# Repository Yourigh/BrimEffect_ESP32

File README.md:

# BrimEffect_ESP32
 ESP32 board with interface for WS2812 LED strip, connected MIC and IR remote receiver, including FW and 3D prited box
 
# 3D prited box

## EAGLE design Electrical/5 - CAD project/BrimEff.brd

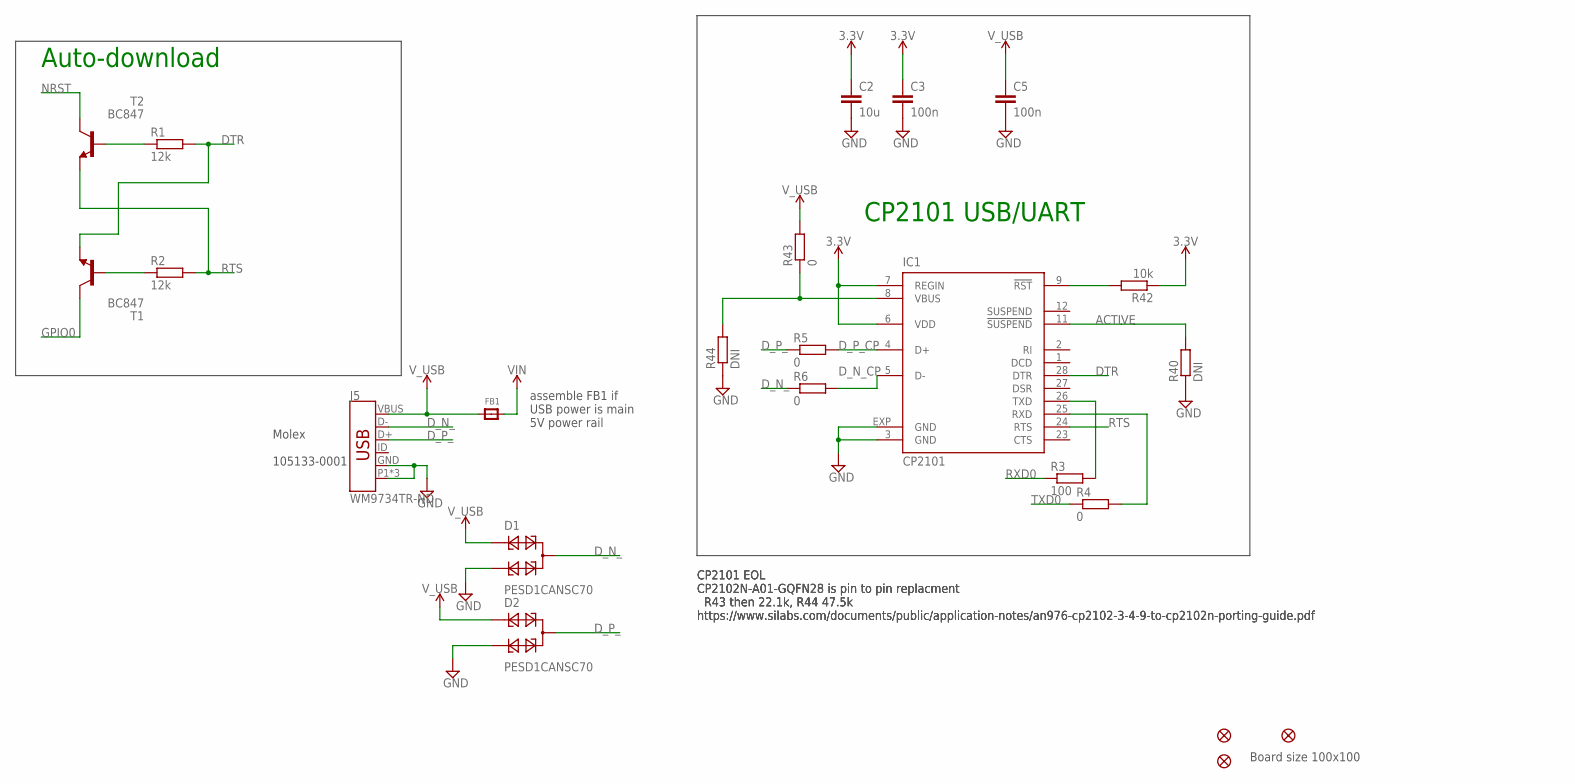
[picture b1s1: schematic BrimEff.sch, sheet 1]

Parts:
C2: 10u; C0603K; PARTNO GRM188R61A106KE69J
C3, C5: 100n; C0603K; PARTNO CC0603KRX7R8BB104
D1, D2: PESD1CANSC70; SOT323-R; PARTNO PESD1CAN-UX
FB1: FERRITE; 0603; PARTNO BLM18PG121SN1D
FID1, FID2, FID4: FIDUCIAL""; FIDUCIAL_1MM
IC1: CP2101; MLP28; PARTNO CP2101-GM
J5: WM9734TR-ND; USB-B-MICRO-SMD_VERT; PARTNO 105133-0001
R1, R2: 12k; R0603; PARTNO RC0603FR-0712KL
R3: 100; R0603; PARTNO CRCW0603100RFKEAC
R4, R5, R6, R43: 0; R0603; PARTNO CRCW06030000Z0EAC
R40, R44: DNI; R0603; PARTNO CRCW06030000Z0EAC
R42: 10k; R0603; PARTNO CRCW060310K0JNEAC
T1, T2: BC847; SOT23; PARTNO BC847A-TP

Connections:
3.3V: C2.1, C3.1, IC1.6 (VDD), IC1.7 (REGIN), R42.1; also elsewhere on the board
ACTIVE: IC1.11 (!SUSPEND), R40.2
DTR: IC1.28 (DTR), R1.2, T1.2 (E)
D_N_: D1.3, J5.D-, R6.1
D_N_CP: IC1.5 (D-), R6.2
D_P_: D2.3, J5.D+, R5.1
D_P_CP: IC1.4 (D+), R5.2
GND: C2.2, C3.2, C5.2, D1.2, D2.2, IC1.3 (GND), IC1.EXP (GND), J5.GND, J5.P1 (SHIELD), J5.P2 (SHIELD), J5.P3 (SHIELD), R40.1, R44.1; also elsewhere on the board
GPIO0: T1.3 (C); also elsewhere on the board
unnamed: R1.1, T2.1 (B)
unnamed: R2.1, T1.1 (B)
unnamed: IC1.9 (!RST), R42.2
unnamed: IC1.8 (VBUS), R43.1, R44.2
NRST: T2.3 (C); also elsewhere on the board
RTS: IC1.24 (RTS), R2.2, T2.2 (E)
RXD0: R3.1; also elsewhere on the board
RXD0_CP2101IN: IC1.26 (TXD), R3.2
TXD0: R4.1; also elsewhere on the board
TXD0_CP2101: IC1.25 (RXD), R4.2
VIN: FB1.2; also elsewhere on the board
V_USB: C5.1, D1.1, D2.1, FB1.1, J5.VBUS, R43.2

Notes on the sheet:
CP2101 USB/UART
Auto-download
Board size 100x100
Molex 105133-0001
CP2101 EOL CP2102N-A01-GQFN28 is pin to pin replacment R43 then 22.1k, R44 47.5k https://www.silabs.com/documents/public/application-notes/an976-cp2102-3-4-9-to-cp2102n-porting-guide.pdf
assemble FB1 if USB power is main 5V power rail

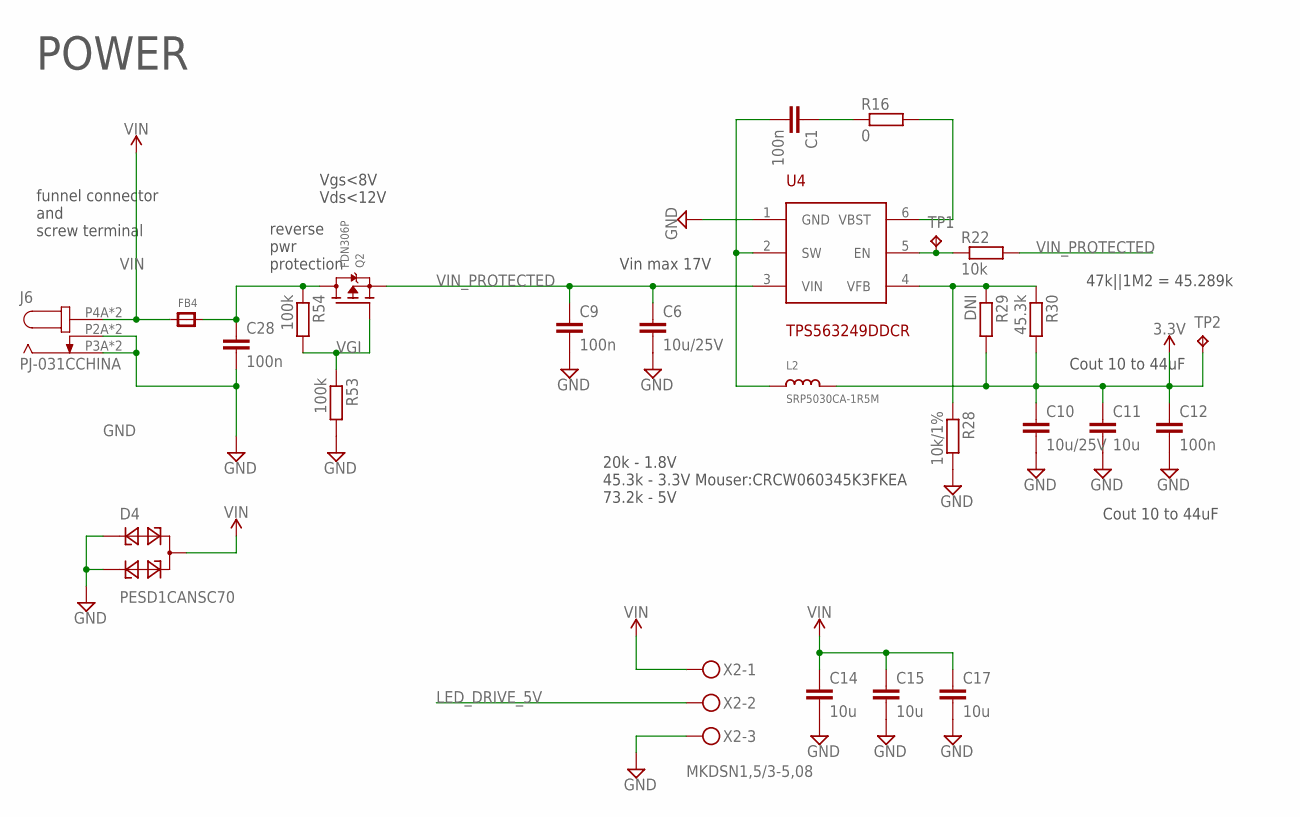
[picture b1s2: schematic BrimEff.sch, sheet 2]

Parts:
C1, C9, C12, C28: 100n; C0603K; PARTNO CC0603KRX7R8BB104
C6, C10: 10u/25V; C0603K; PARTNO GRM188R61E106KA73J
C11, C14, C15, C17: 10u; C0603K; PARTNO GRM188R61A106KE69J
D4: PESD1CANSC70; SOT323-R; PARTNO PESD1CAN-UX
FB4: FERRITE; 0603; PARTNO BLM18PG121SN1D
J6: PJ-031CCHINA; DC-005_5.5X2.1MM_JACK
L2: SRP5030CA-1R5M; SRP5030CA; PARTNO SRP5030CA-1R5M
Q2: FDN306P; SOT23-WIDE; PARTNO FDN306P
R16: 0; R0603; PARTNO CRCW06030000Z0EAC
R22: 10k; R0603; PARTNO CRCW060310K0JNEAC
R28: 10k/1%; R0603; PARTNO RN73R1JTTD1002D25
R29: DNI; R0603
R30: 45.3k; R0603; PARTNO ERJ-PB3D4532V
R53, R54: 100k; R0603; PARTNO CRCW0603100KFKEAC
TP1, TP2: TPTP10R; TP10R
U4: TPS563249DDCR; SOT23-6; PARTNO TPS563249DDCR
X2: MKDSN1,5/3-5,08

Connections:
3.3V: C10.1, C11.1, C12.1, L2.P$2 (2), R29.2, R30.2, TP2.TP; also elsewhere on the board
GND: C6.2, C9.2, C10.2, C11.2, C12.2, C14.2, C15.2, C17.2, C28.2, D4.1, D4.2, J6.P2A (3), J6.P2B (3), J6.P3A (2), J6.P3B (2), R28.2, R53.2, U4.1 (GND), X2.3; also elsewhere on the board
LED_DRIVE_5V: X2.2; also elsewhere on the board
unnamed: C1.1, R16.1
unnamed: C28.1, FB4.2, Q2.3 (D), R54.1
unnamed: R16.2, U4.6 (VBST)
unnamed: C1.2, L2.P$1 (1), U4.2 (SW)
unnamed: R22.1, TP1.TP, U4.5 (EN)
unnamed: R28.1, R29.1, R30.1, U4.4 (VFB)
VGI: Q2.1 (G), R53.1, R54.2
VIN: C14.1, C15.1, C17.1, D4.3, FB4.1, J6.P4A (1), J6.P4B (1), X2.1; also elsewhere on the board
VIN_PROTECTED: C6.1, C9.1, Q2.2 (S), R22.2, U4.3 (VIN); also elsewhere on the board

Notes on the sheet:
POWER
20k - 1.8V 45.3k - 3.3V Mouser:CRCW060345K3FKEA 73.2k - 5V
Cout 10 to 44uF
reverse pwr protection
Vgs<8V Vds<12V
Vin max 17V
funnel connector and screw terminal
47k||1M2 = 45.289k

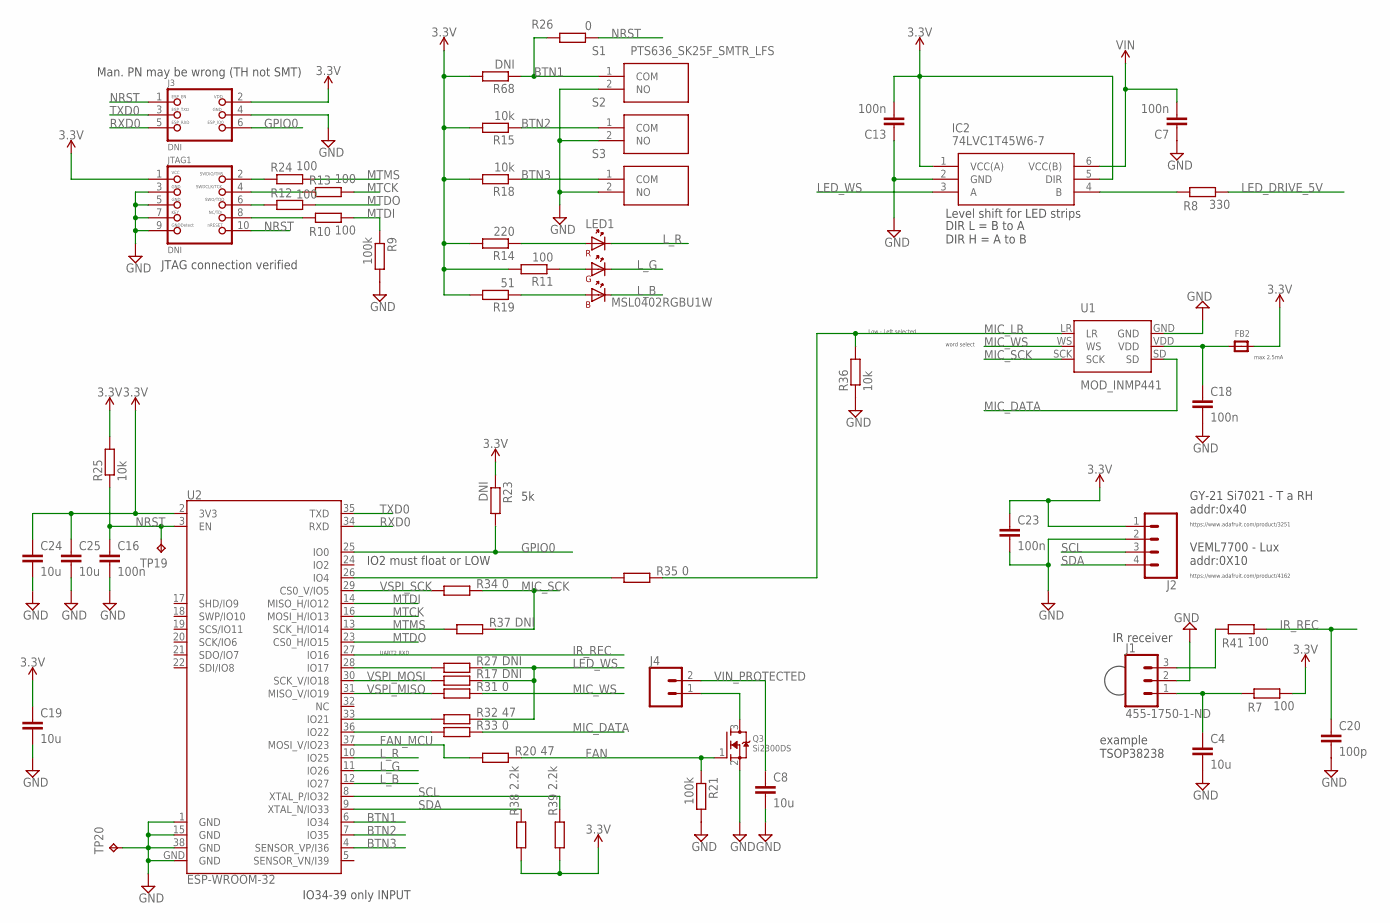
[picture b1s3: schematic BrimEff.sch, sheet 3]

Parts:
C4, C8, C19, C24, C25: 10u; C0603K; PARTNO GRM188R61A106KE69J
C7, C13, C16, C18, C23: 100n; C0603K; PARTNO CC0603KRX7R8BB104
C20: 100p; C0603K; PARTNO GRM188R61A106KE69J
FB2: FERRITE; 0603; PARTNO BLM18PG121SN1D
IC2: 74LVC1T45W6-7; SOT95P285X140-6N
J1: 455-1750-1-ND; 1X03
J2: CONN_04PTH; 1X04
J3: DNI; 2X03_1.27MM_SMT; PARTNO HTMS-103-03-T-D-SM
J4: CONN_02; 1X02
JTAG1: DNI; 2X05_1.27MM_SMT; PARTNO M50-3600542R
LED1: MSL0402RGBU1W; MSL0402RGBU1-W
Q3: Si2300DS; SOT23; PARTNO SI2300DS-T1-GE3
R7, R10, R11, R12, R13, R24, R41: 100; R0603; PARTNO CRCW0603100RFKEAC
R8: 330; R0603; PARTNO CRCW0603100RFKEAC
R9, R21: 100k; R0603; PARTNO CRCW0603100KFKEAC
R14: 220; R0603; PARTNO CRCW0603100RFKEAC
R15, R18, R25, R36: 10k; R0603; PARTNO CRCW060310K0JNEAC
R17, R27, R37: DNI; R0603; PARTNO CRCW060347R0FKEAC
R19: 51; R0603; PARTNO CRCW0603100RFKEAC
R20, R32: 47; R0603; PARTNO CRCW060347R0FKEAC
R23: DNI; R0603; PARTNO CRCW06030000Z0EAC
R26: 0; R0603; PARTNO CRCW060310K0JNEAC
R31, R33, R34, R35: 0; R0603; PARTNO CRCW060347R0FKEAC
R38, R39: 2.2k; R0603; PARTNO CRCW060347R0FKEAC
R68: DNI; R0603; PARTNO CRCW060310K0JNEAC
S1, S2, S3: PTS636_SK25F_SMTR_LFS; PTS636SK25FSMTRLFS
TP19, TP20: TPTP10R; TP10R
U1: MOD_INMP441
U2: ESP-WROOM-32; PARTNO ESP32-WROOM-32

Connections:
3.3V: C13.2, C19.1, C23.1, C24.1, C25.1, FB2.2, IC2.1 (VCC(A)), IC2.5 (DIR), J2.1, J3.2, JTAG1.1, R7.2, R11.2, R14.2, R15.2, R18.2, R19.2, R23.1, R25.2, R38.1, R39.1, R68.2, U2.2 (3V3); also elsewhere on the board
BTN1: R26.2, R68.1, S1.1 (COM), U2.6 (IO34)
BTN2: R15.1, S2.1 (COM), U2.7 (IO35)
BTN3: R18.1, S3.1 (COM), U2.4 (SENSOR_VP/I36)
FAN: Q3.1 (G), R20.2, R21.1
FAN_MCU: R20.1, U2.37 (MOSI_V/IO23)
GND: C4.2, C7.1, C8.2, C13.1, C16.2, C18.2, C19.2, C20.2, C23.2, C24.2, C25.2, IC2.2 (GND), J1.2, J2.2, J3.4, JTAG1.3, JTAG1.5, JTAG1.7, JTAG1.9, Q3.2 (S), R9.2, R21.2, R36.1, S1.2 (NO), S2.2 (NO), S3.2 (NO), TP20.TP, U1.GND, U2.1 (GND), U2.15 (GND), U2.38 (GND), U2.GND; also elsewhere on the board
GPIO0: J3.6, R23.2, U2.25 (IO0); also elsewhere on the board
IR_REC: C20.1, R41.2, U2.27 (IO16)
LED_DRIVE_5V: R8.2; also elsewhere on the board
LED_WS: IC2.3 (A), R17.2, R27.2, R32.2
L_B: LED1.1 (K_B), U2.12 (IO27)
L_G: LED1.2 (K_G), U2.11 (IO26)
L_R: LED1.3 (K_R), U2.10 (IO25)
MIC_DATA: R33.2, U1.SD
MIC_LR: R35.2, R36.2, U1.LR
MIC_SCK: R34.2, R37.2, U1.SCK
MIC_WS: R31.2, U1.WS
MTCK: R13.2, U2.16 (MOSI_H/IO13)
MTDI: R9.1, R10.2, U2.14 (MISO_H/IO12)
MTDO: R12.2, U2.23 (CS0_H/IO15)
MTMS: R24.2, R37.1, U2.13 (SCK_H/IO14)
unnamed: J1.3, R41.1
unnamed: LED1.6 (A_B), R19.1
unnamed: J4.1, Q3.3 (D)
unnamed: C4.1, J1.1, R7.1
unnamed: IC2.4 (B), R8.1
unnamed: LED1.5 (A_G), R11.1
unnamed: C18.1, FB2.1, U1.VDD
unnamed: R27.1, U2.28 (IO17)
unnamed: R32.1, U2.33 (IO21)
unnamed: LED1.4 (A_R), R14.1
unnamed: R33.1, U2.36 (IO22)
unnamed: R35.1, U2.26 (IO4)
NRST: C16.1, J3.1, JTAG1.10, R25.1, R26.1, TP19.TP, U2.3 (EN); also elsewhere on the board
RXD0: J3.5, U2.34 (RXD); also elsewhere on the board
SCL: J2.3, R39.2, U2.8 (XTAL_P/IO32)
SDA: J2.4, R38.2, U2.9 (XTAL_N/IO33)
TCKCONN: JTAG1.4, R13.1
TDICONN: JTAG1.8, R10.1
TDOCONN: JTAG1.6, R12.1
TMSCONN: JTAG1.2, R24.1
TXD0: J3.3, U2.35 (TXD); also elsewhere on the board
VIN: C7.2, IC2.6 (VCC(B)); also elsewhere on the board
VIN_PROTECTED: C8.1, J4.2; also elsewhere on the board
VSPI_MISO: R31.1, U2.31 (MISO_V/IO19)
VSPI_MOSI: R17.1, U2.30 (SCK_V/IO18)
VSPI_SCK: R34.1, U2.29 (CS0_V/IO5)

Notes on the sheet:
JTAG connection verified
IO34-39 only INPUT
IO2 must float or LOW
Man. PN may be wrong (TH not SMT)
VEML7700 - Lux addr:0X10
https://www.adafruit.com/product/4162
https://www.adafruit.com/product/3251
GY-21 Si7021 - T a RH addr:0x40
Level shift for LED strips
IR receiver
example TSOP38238
DIR L = B to A DIR H = A to B
word select
UART2 RXD
max 2.5mA
Low - Left selected

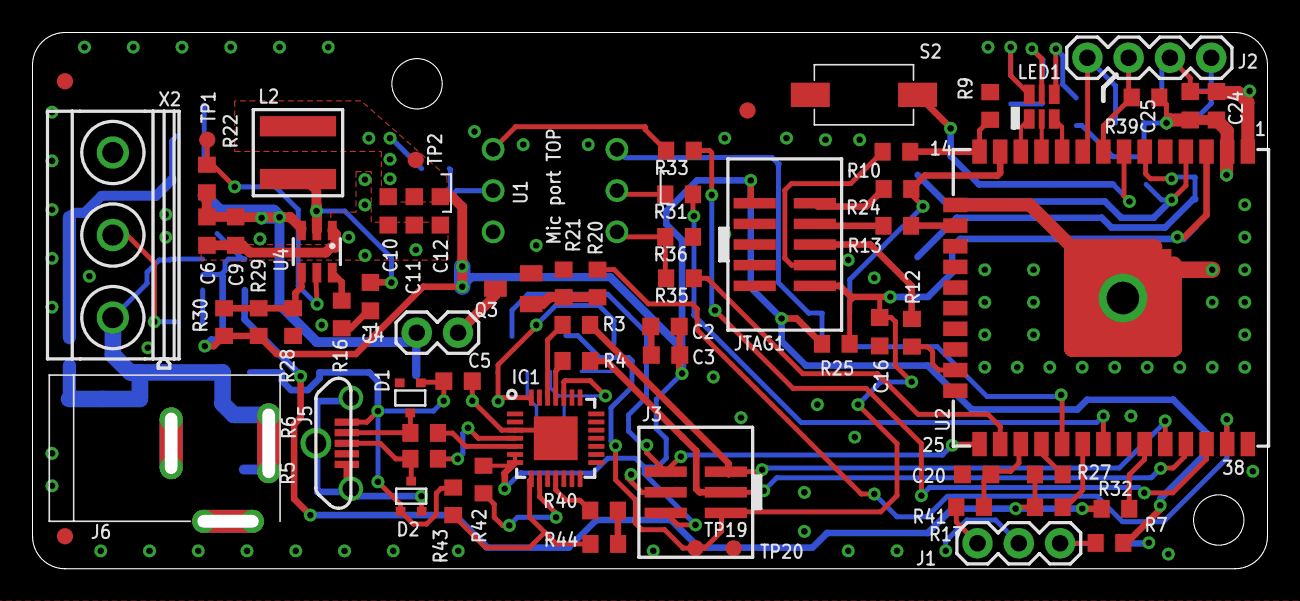
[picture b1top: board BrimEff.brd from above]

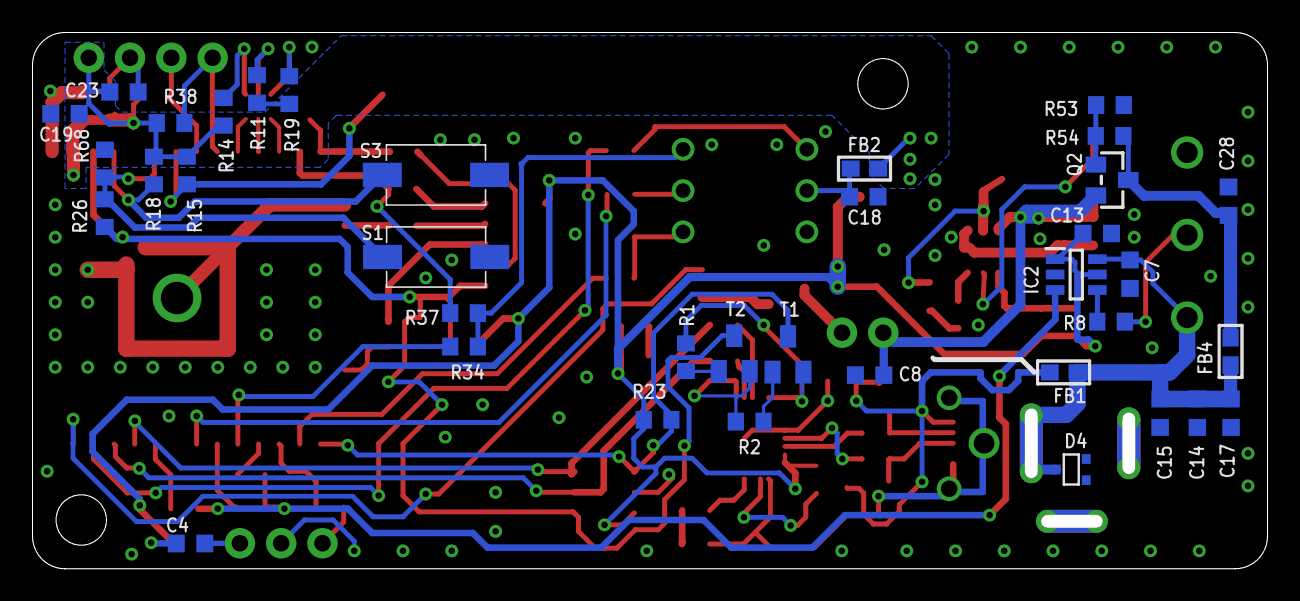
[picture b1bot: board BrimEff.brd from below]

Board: 2 copper layers, 75.2 x 32.2 mm, 106 parts (37 on the bottom side), 69 nets.

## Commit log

2020-04-05 first version
2020-04-05 3d design update
2020-04-07 3d model update
2020-04-07 pic update
2020-04-08 3d print export
2020-04-24 mic module step
2020-06-14 News
2020-10-10 update main
2020-10-11 added datasheets

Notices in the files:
parts and their libraries:
SparkFun-Retired: Licensing: Creative Commons ShareAlike 4.0 International - https://creativecommons.org/licenses/by-sa/4.0
microbuilder: This work is placed in the public domain, and may be freely used for commercial and non-commercial work with the following conditions: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
